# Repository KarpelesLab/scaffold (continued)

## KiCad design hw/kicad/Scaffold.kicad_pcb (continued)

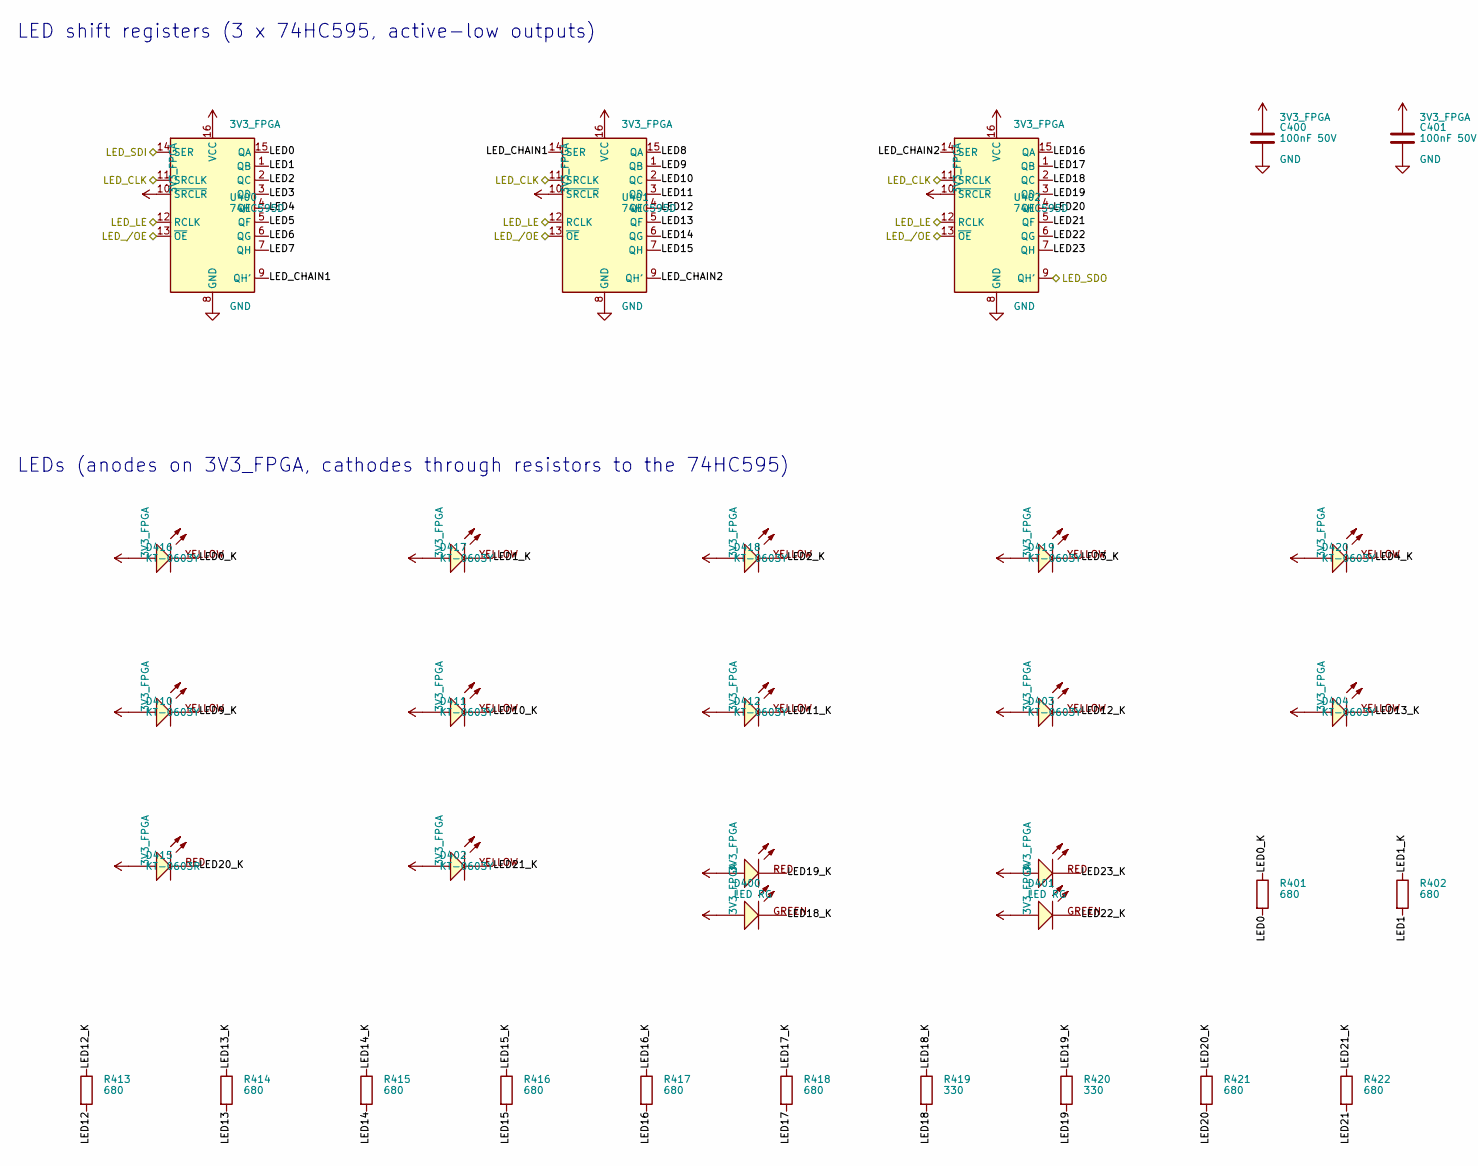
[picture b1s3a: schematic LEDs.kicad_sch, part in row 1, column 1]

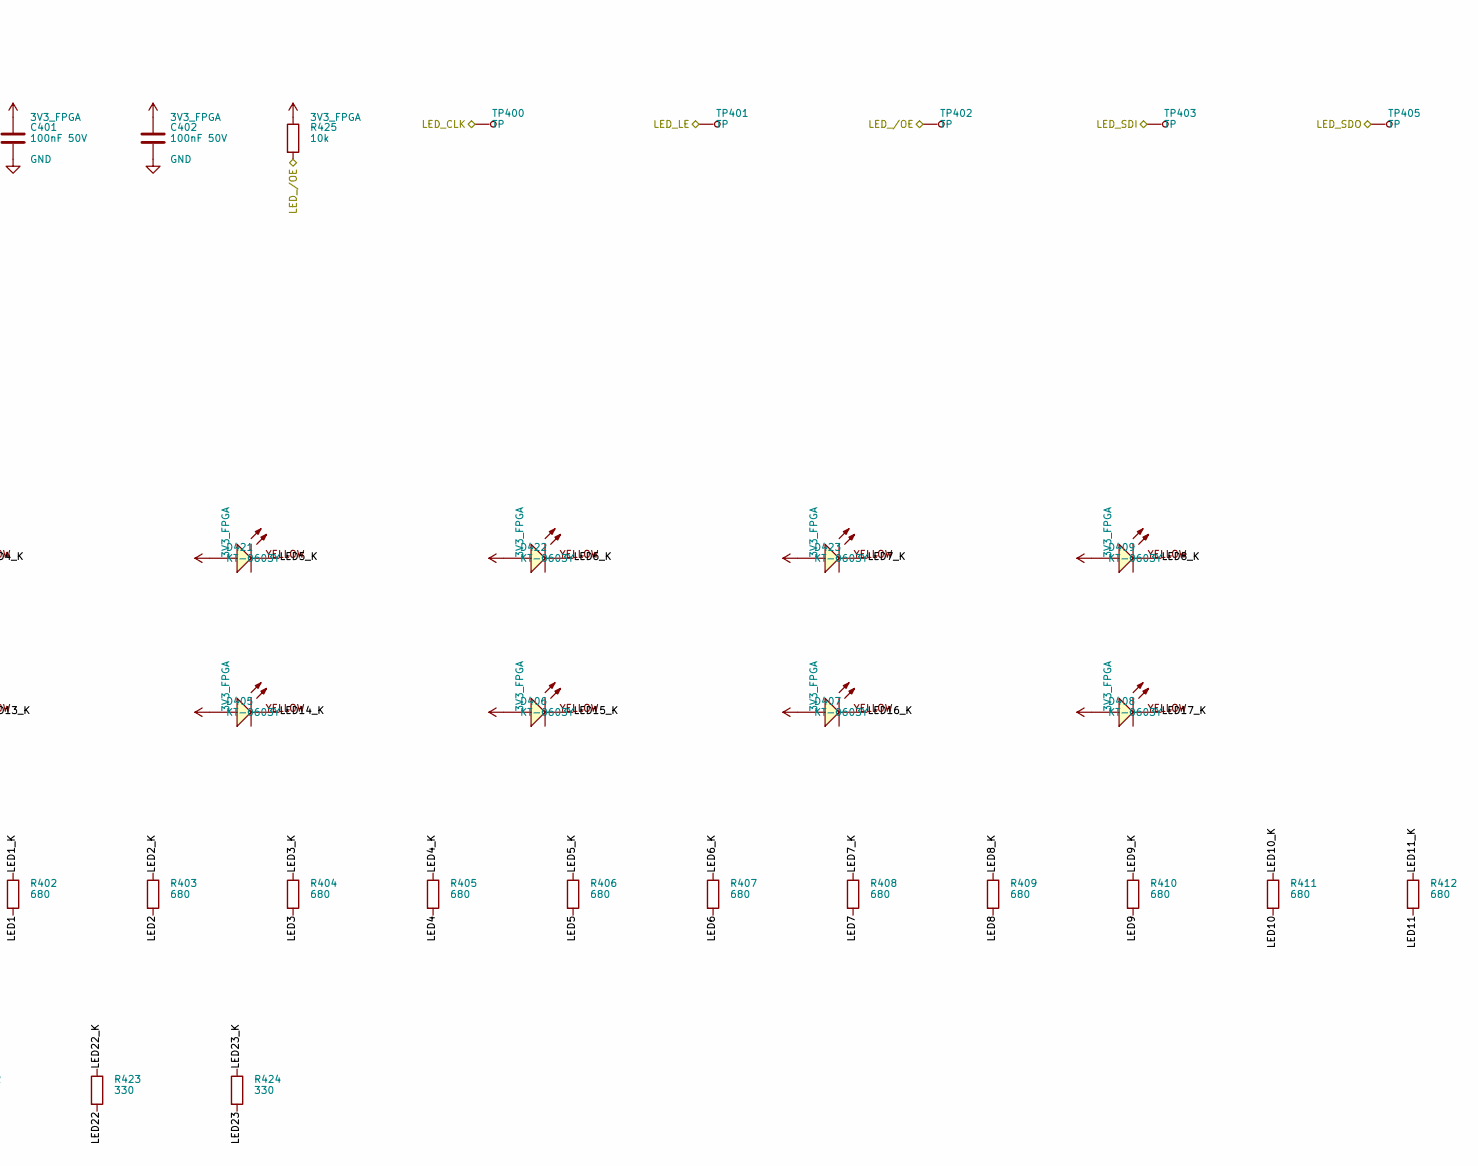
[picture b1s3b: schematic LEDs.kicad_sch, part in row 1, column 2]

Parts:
C400, C401, C402: 100nF 50V; C_0603_1608Metric; LCSC C14663
D400, D401: LED RG; PLCC-4_3528; MANUFACTURER PN 150141RV73100; LCSC C5872444
D402, D403, D404, D405, D406, D407, D408, D409, D410, D411, D412, D416, D417, D418, D419, D420, D421, D422, D423: KT-0603Y; LED_0603_1608Metric; MANUFACTURER PN KT-0603Y; LCSC C2287
D415: KT-0603R; LED_0603_1608Metric; MANUFACTURER PN KT-0603R; LCSC C2286
R401, R402, R403, R404, R405, R406, R407, R408, R409, R410, R411, R412, R413, R414, R415, R416, R417, R418, R421, R422: 680; R_0603_1608Metric; LCSC C23228
R419, R420, R423, R424: 330; R_0603_1608Metric; LCSC C23138
R425: 10k; R_0603_1608Metric; LCSC C25804
TP400, TP401, TP402, TP403, TP405: TP; TP_001
U400, U401, U402: 74HC595D; SOIC-16_3.9x9.9mm_P1.27mm; MANUFACTURER PN 74HC595D,118; LCSC C5947

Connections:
3V3_FPGA: C400.1, C401.1, C402.1, D400.1 (AR), D400.2 (AG), D401.1 (AR), D401.2 (AG), D402.2 (A), D403.2 (A), D404.2 (A), D405.2 (A), D406.2 (A), D407.2 (A), D408.2 (A), D409.2 (A), D410.2 (A), D411.2 (A), D412.2 (A), D415.2 (A), D416.2 (A), D417.2 (A), D418.2 (A), D419.2 (A), D420.2 (A), D421.2 (A), D422.2 (A), D423.2 (A), R425.1, U400.10 (~SRCLR), U400.16 (VCC), U401.10 (~SRCLR), U401.16 (VCC), U402.10 (~SRCLR), U402.16 (VCC); also elsewhere on the board
/U_FPGA/LED_CLK: TP400.1, U400.11 (SRCLK), U401.11 (SRCLK), U402.11 (SRCLK); also elsewhere on the board
/U_FPGA/LED_LE: TP401.1, U400.12 (RCLK), U401.12 (RCLK), U402.12 (RCLK); also elsewhere on the board
/U_FPGA/LED_SDI: TP403.1, U400.14 (SER); also elsewhere on the board
/U_FPGA/LED_SDO: TP405.1, U402.9 (QH'); also elsewhere on the board
/U_FPGA/LED_/OE: R425.2, TP402.1, U400.13 (~OE), U401.13 (~OE), U402.13 (~OE); also elsewhere on the board
/U_LEDs/LED0: R401.2, U400.15 (QA)
/U_LEDs/LED0_K: D416.1 (K), R401.1
/U_LEDs/LED1: R402.2, U400.1 (QB)
/U_LEDs/LED1_K: D417.1 (K), R402.1
/U_LEDs/LED2: R403.2, U400.2 (QC)
/U_LEDs/LED2_K: D418.1 (K), R403.1
/U_LEDs/LED3: R404.2, U400.3 (QD)
/U_LEDs/LED3_K: D419.1 (K), R404.1
/U_LEDs/LED4: R405.2, U400.4 (QE)
/U_LEDs/LED4_K: D420.1 (K), R405.1
/U_LEDs/LED5: R406.2, U400.5 (QF)
/U_LEDs/LED5_K: D421.1 (K), R406.1
/U_LEDs/LED6: R407.2, U400.6 (QG)
/U_LEDs/LED6_K: D422.1 (K), R407.1
/U_LEDs/LED7: R408.2, U400.7 (QH)
/U_LEDs/LED7_K: D423.1 (K), R408.1
/U_LEDs/LED8: R409.2, U401.15 (QA)
/U_LEDs/LED8_K: D409.1 (K), R409.1
/U_LEDs/LED9: R410.2, U401.1 (QB)
/U_LEDs/LED9_K: D410.1 (K), R410.1
/U_LEDs/LED10: R411.2, U401.2 (QC)
/U_LEDs/LED10_K: D411.1 (K), R411.1
/U_LEDs/LED11: R412.2, U401.3 (QD)
/U_LEDs/LED11_K: D412.1 (K), R412.1
/U_LEDs/LED12: R413.2, U401.4 (QE)
/U_LEDs/LED12_K: D403.1 (K), R413.1
/U_LEDs/LED13: R414.2, U401.5 (QF)
/U_LEDs/LED13_K: D404.1 (K), R414.1
/U_LEDs/LED14: R415.2, U401.6 (QG)
/U_LEDs/LED14_K: D405.1 (K), R415.1
/U_LEDs/LED15: R416.2, U401.7 (QH)
/U_LEDs/LED15_K: D406.1 (K), R416.1
/U_LEDs/LED16: R417.2, U402.15 (QA)
/U_LEDs/LED16_K: D407.1 (K), R417.1
/U_LEDs/LED17: R418.2, U402.1 (QB)
/U_LEDs/LED17_K: D408.1 (K), R418.1
/U_LEDs/LED18: R419.2, U402.2 (QC)
/U_LEDs/LED18_K: D400.4 (KG), R419.1
/U_LEDs/LED19: R420.2, U402.3 (QD)
/U_LEDs/LED19_K: D400.3 (KR), R420.1
/U_LEDs/LED20: R421.2, U402.4 (QE)
/U_LEDs/LED20_K: D415.1 (K), R421.1
/U_LEDs/LED21: R422.2, U402.5 (QF)
/U_LEDs/LED21_K: D402.1 (K), R422.1
/U_LEDs/LED22: R423.2, U402.6 (QG)
/U_LEDs/LED22_K: D401.4 (KG), R423.1
/U_LEDs/LED23: R424.2, U402.7 (QH)
/U_LEDs/LED23_K: D401.3 (KR), R424.1
/U_LEDs/LED_CHAIN1: U400.9 (QH'), U401.14 (SER)
/U_LEDs/LED_CHAIN2: U401.9 (QH'), U402.14 (SER)
GND: C400.2, C401.2, C402.2, U400.8 (GND), U401.8 (GND), U402.8 (GND); also elsewhere on the board

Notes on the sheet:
LED shift registers (3 x 74HC595, active-low outputs)
LEDs (anodes on 3V3_FPGA, cathodes through resistors to the 74HC595)
